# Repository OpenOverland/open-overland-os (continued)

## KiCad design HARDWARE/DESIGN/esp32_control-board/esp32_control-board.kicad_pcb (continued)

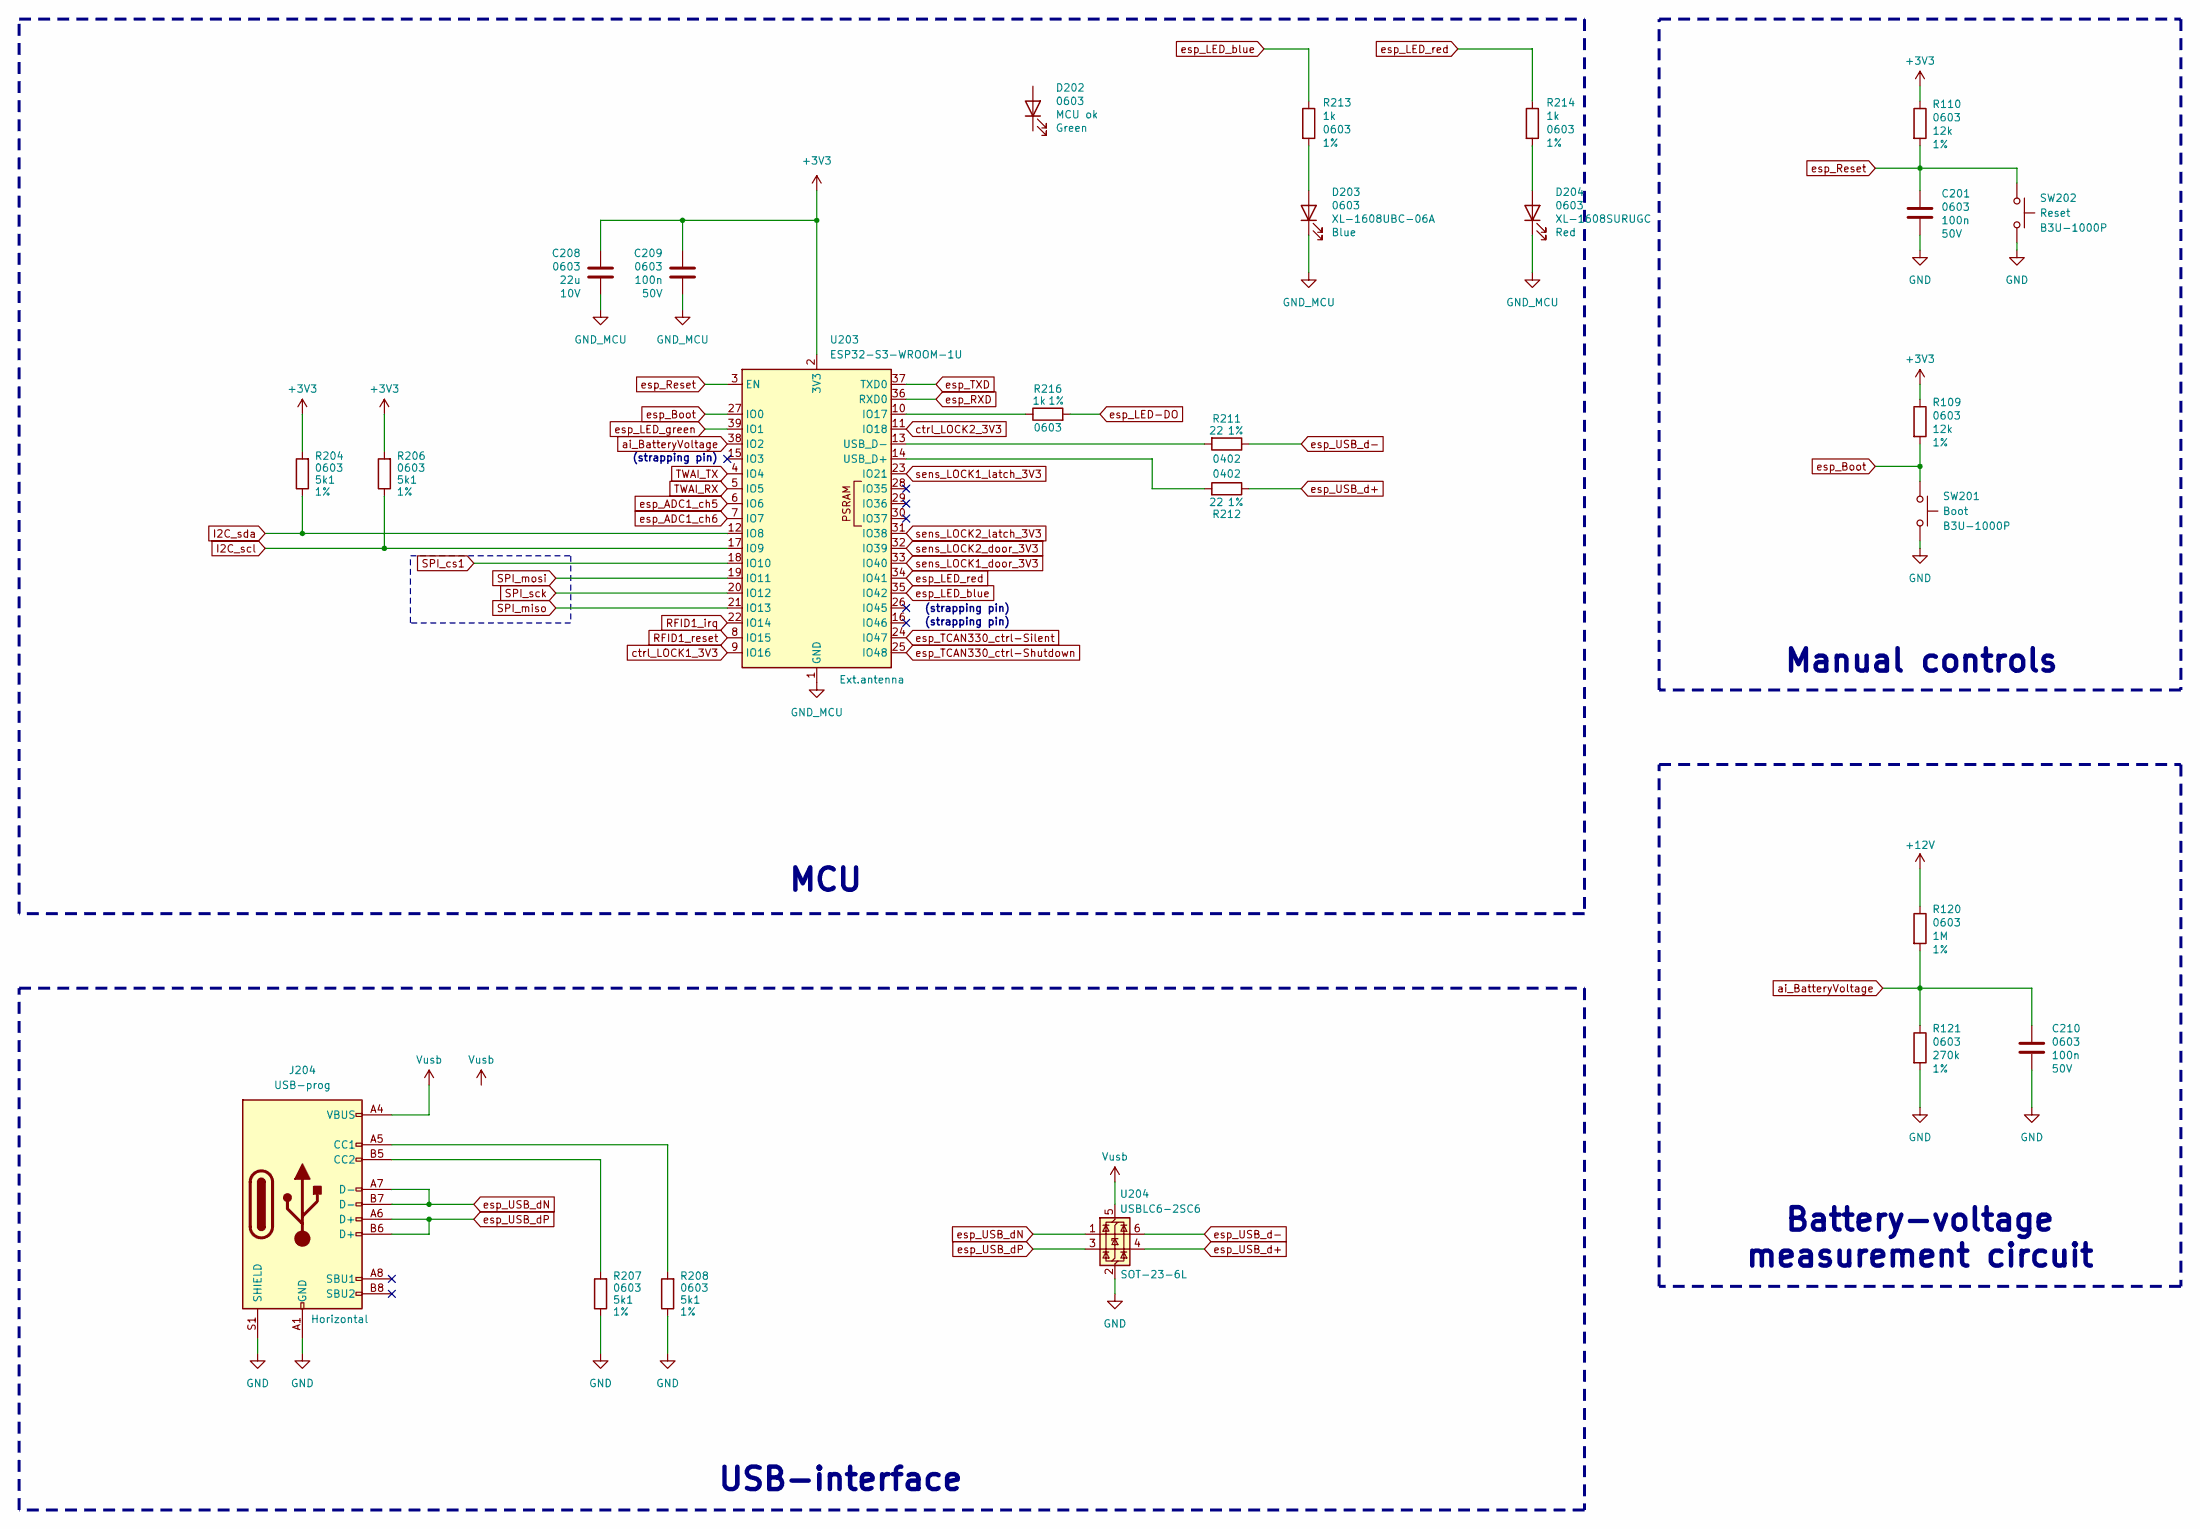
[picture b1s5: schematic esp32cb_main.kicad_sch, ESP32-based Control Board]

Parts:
C201, C209, C210: 100n; C_0603_1608Metric; LCSC part C1591
C208: 22u; C_0805_2012Metric; LCSC C907991
D202: MCU ok; LED_0603_1608Metric; LCSC part C965804
D203: XL-1608UBC-06A; LED_0603_1608Metric; LCSC C7371904
D204: XL-1608SURUGC; LED_0603_1608Metric; LCSC C5349934
J204: USB-prog; C3151749_USB_TYPE-C_Vertical
R109, R110: 12k; R_0603_1608Metric; LCSC C114659
R120: 1M; R_0603_1608Metric; LCSC C22935
R121: 270k; R_0603_1608Metric; LCSC C22965
R204, R206, R207, R208: 5k1; R_0603_1608Metric; LCSC part C2907044
R211, R212: 22; R_0402_1005Metric; LCSC part C114765
R213, R214, R216: 1k; R_0603_1608Metric; LCSC part C21190
SW201: Boot; SW_SPST_B3U-1000P; LCSC part C231329
SW202: Reset; SW_SPST_B3U-1000P; LCSC part C231329
U203: ESP32-S3-WROOM-1U; LCSC C3013946
U204: USBLC6-2SC6; SOT-23-6; LCSC part C7519

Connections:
+3V3: C208.2, C209.2, R109.1, R110.1, R204.2, R206.2, U203.2 (3V3); also elsewhere on the board
+12V: R120.1; also elsewhere on the board
GND: C201.1, C210.1, J204.A1 (GND), J204.A12 (GND), J204.B1 (GND), J204.B12 (GND), J204.S1 (SHIELD), R121.2, R207.1, R208.1, SW201.2, SW202.2, U204.2 (GND); also elsewhere on the board
GND_MCU: C208.1, C209.1, D203.1 (K), D204.1 (K), U203.1 (GND), U203.40 (GND), U203.41 (GND); also elsewhere on the board
I2C_scl: R206.1, U203.17 (IO9); also elsewhere on the board
I2C_sda: R204.1, U203.12 (IO8); also elsewhere on the board
unnamed: D203.2 (A), R213.2
unnamed: D204.2 (A), R214.2
unnamed: J204.A5 (CC1), R208.2
unnamed: J204.B5 (CC2), R207.2
unnamed: R216.1, U203.10 (IO17)
unnamed: R212.2, U203.14 (USB_D+)
unnamed: R211.2, U203.13 (USB_D-)
RFID1_irq: U203.22 (IO14); also elsewhere on the board
RFID1_reset: U203.8 (IO15); also elsewhere on the board
SPI_cs1: U203.18 (IO10); also elsewhere on the board
SPI_miso: U203.21 (IO13); also elsewhere on the board
SPI_mosi: U203.19 (IO11); also elsewhere on the board
SPI_sck: U203.20 (IO12); also elsewhere on the board
TWAI_RX: U203.5 (IO5); also elsewhere on the board
TWAI_TX: U203.4 (IO4); also elsewhere on the board
Vusb: J204.A4 (VBUS), J204.A9 (VBUS), J204.B4 (VBUS), J204.B9 (VBUS), U204.5 (VBUS); also elsewhere on the board
ai_BatteryVoltage: C210.2, R120.2, R121.1, U203.38 (IO2)
ctrl_LOCK1_3V3: U203.9 (IO16); also elsewhere on the board
ctrl_LOCK2_3V3: U203.11 (IO18); also elsewhere on the board
esp_ADC1_ch5: U203.6 (IO6); also elsewhere on the board
esp_ADC1_ch6: U203.7 (IO7); also elsewhere on the board
esp_Boot: R109.2, SW201.1, U203.27 (IO0)
esp_LED-DO: R216.2; also elsewhere on the board
esp_LED_blue: R213.1, U203.35 (IO42)
esp_LED_green: U203.39 (IO1)
esp_LED_red: R214.1, U203.34 (IO41)
esp_RXD: U203.36 (RXD0); also elsewhere on the board
esp_Reset: C201.2, R110.2, SW202.1, U203.3 (EN)
esp_TCAN330_ctrl-Shutdown: U203.25 (IO48); also elsewhere on the board
esp_TCAN330_ctrl-Silent: U203.24 (IO47); also elsewhere on the board
esp_TXD: U203.37 (TXD0); also elsewhere on the board
esp_USB_d+: R212.1, U204.4 (I/O2)
esp_USB_d-: R211.1, U204.6 (I/O1)
esp_USB_dN: J204.A7 (D-), J204.B7 (D-), U204.1 (I/O1)
esp_USB_dP: J204.A6 (D+), J204.B6 (D+), U204.3 (I/O2)
sens_LOCK1_door_3V3: U203.33 (IO40); also elsewhere on the board
sens_LOCK1_latch_3V3: U203.23 (IO21); also elsewhere on the board
sens_LOCK2_door_3V3: U203.32 (IO39); also elsewhere on the board
sens_LOCK2_latch_3V3: U203.31 (IO38); also elsewhere on the board

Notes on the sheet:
Battery-voltage measurement circuit
(strapping pin)
USB-interface
MCU
Manual controls

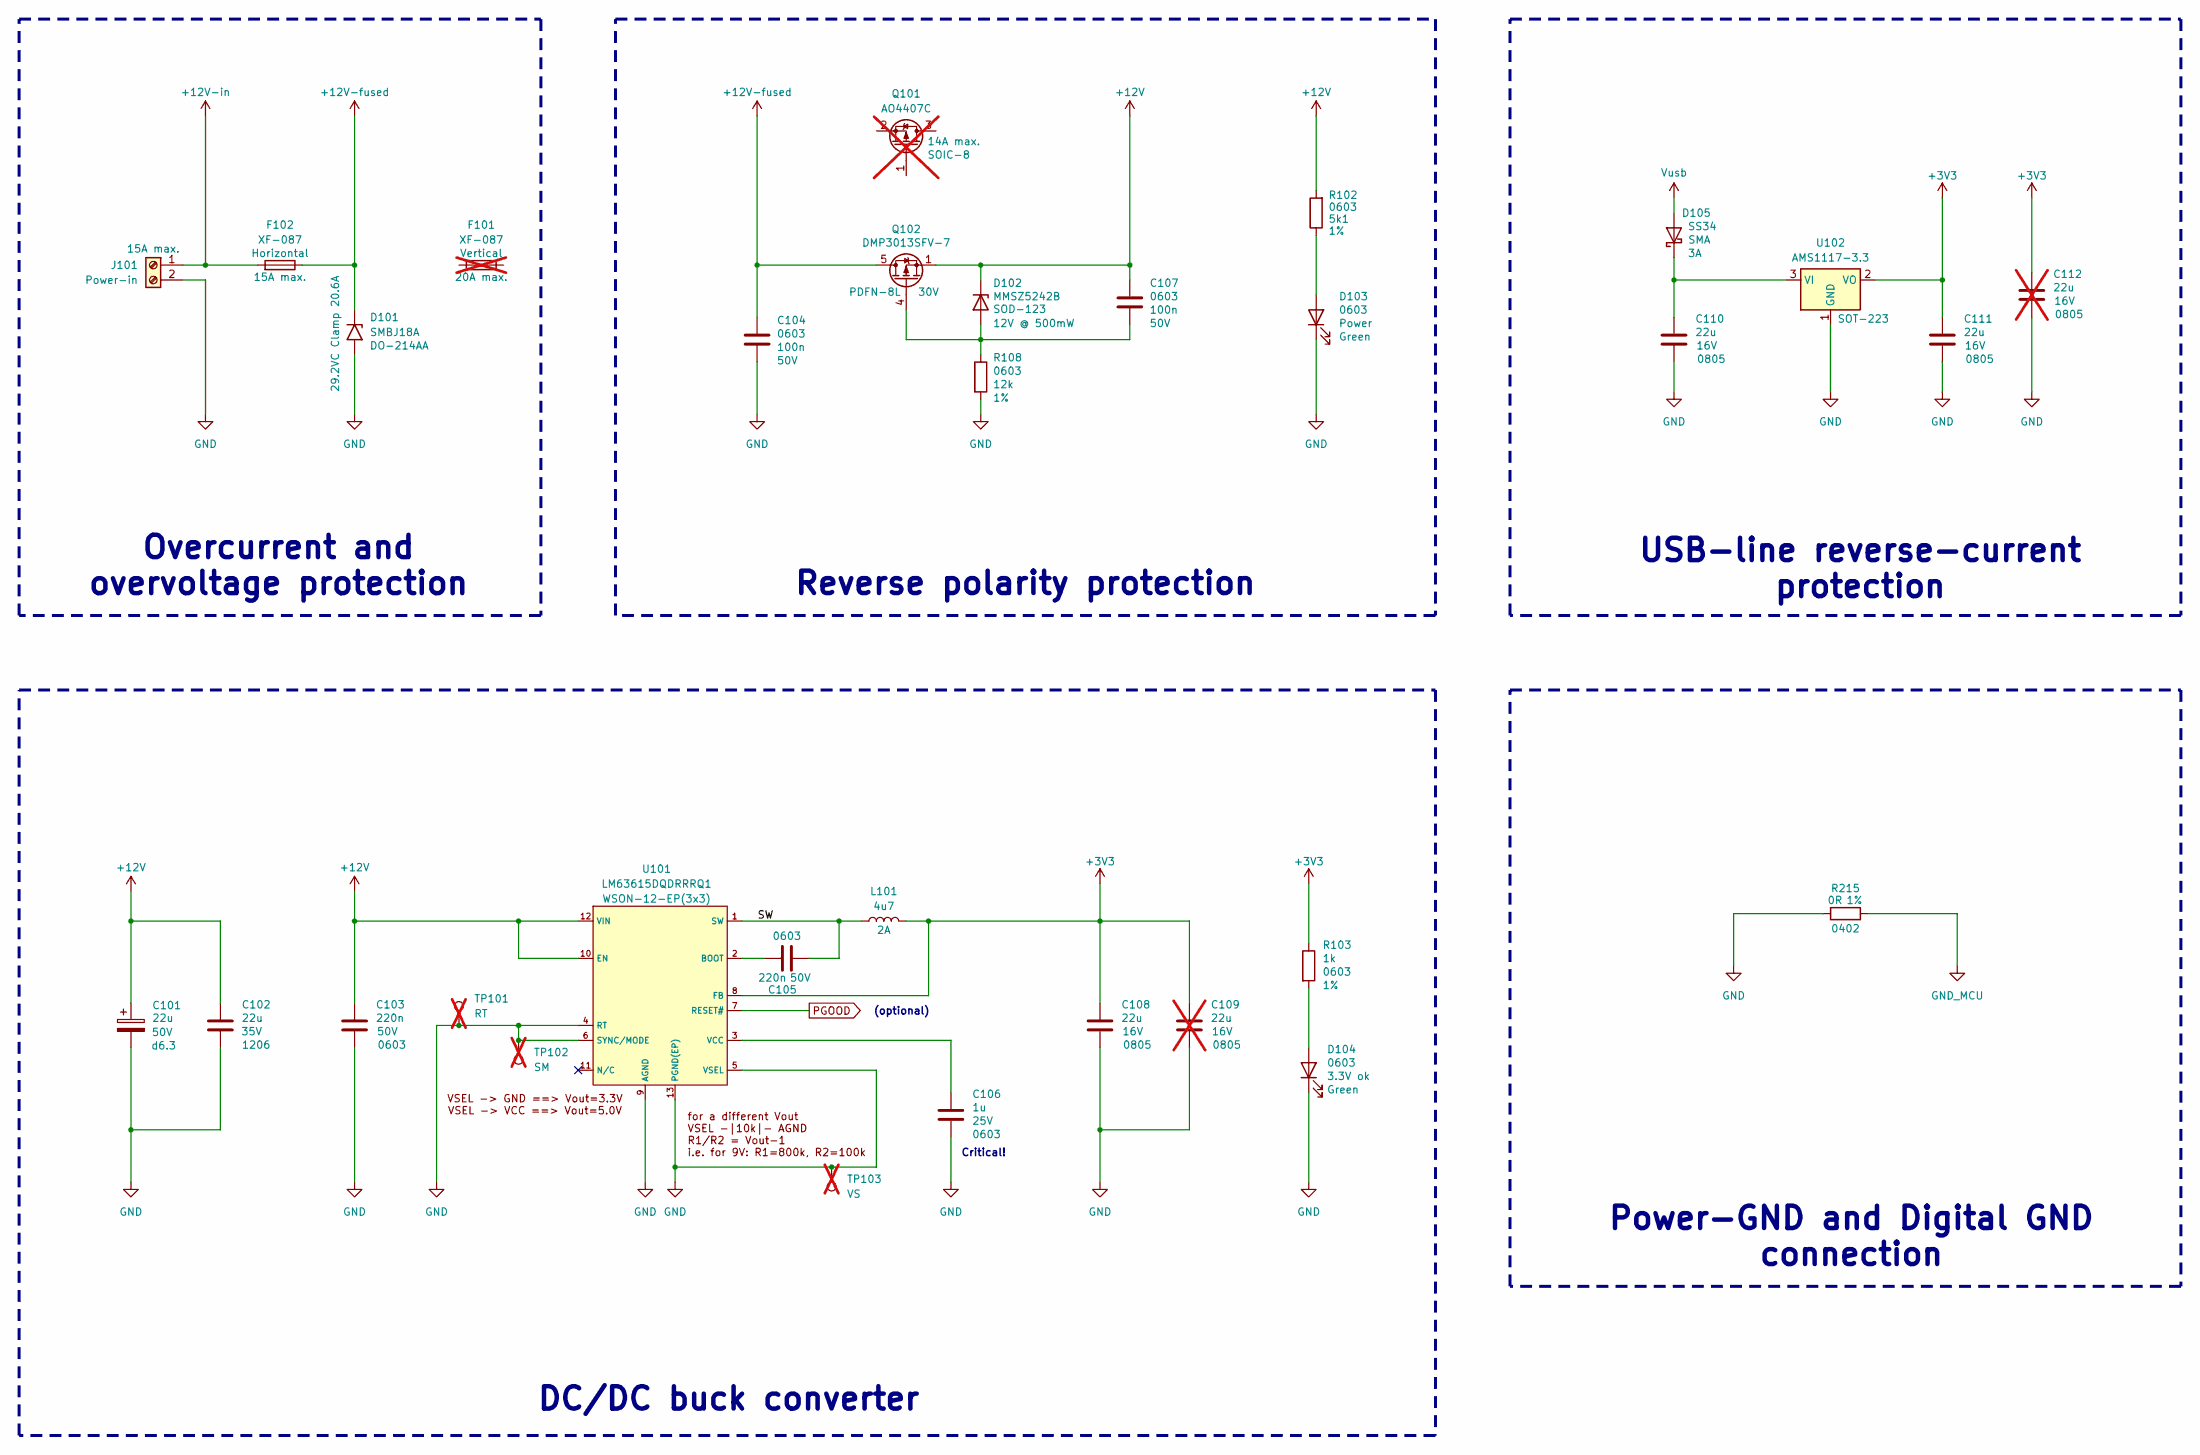
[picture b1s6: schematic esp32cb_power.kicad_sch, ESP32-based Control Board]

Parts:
C101: 22u; CP_Elec_6.3x5.7; LCSC part C2983377
C102: 22u; C_1206_3216Metric; LCSC part C342620
C103, C105: 220n; C_0603_1608Metric; LCSC part C64705
C104, C107: 100n; C_0603_1608Metric; LCSC part C1591
C106: 1u; C_0603_1608Metric; LCSC part C29936
C108, C110, C111: 22u; C_0805_2012Metric; LCSC part C98190
C109, C112: 22u; C_0805_2012Metric; LCSC part C98190; not fitted
D101: SMBJ18A; D_SMB; LCSC C151256
D102: MMSZ5242B; D_SOD-123; LCSC C82050
D103: Power; LED_0603_1608Metric; LCSC part C965804
D104: 3.3V ok; LED_0603_1608Metric; LCSC part C965804
D105: SS34; D_SMA; LCSC part C908680
F101: XF-087; FuseHolder_Blade_ATO_Littelfuse_FLR_178.6165; LCSC C41371864; not fitted
F102: XF-087; C206906_LittleFuse_01530007Z; LCSC C206906
J101: Power-in; AMASS_XT30PW-M_1x02_P2.50mm_Horizontal; LCSC C431092
L101: 4u7; L_Taiyo-Yuden_MD-4040; LCSC part C167828
Q101: AO4407C; SOIC-8_P-MOSFET; LCSC C469397; not fitted
Q102: DMP3013SFV-7; Diodes_PowerDI3333-8; LCSC C264098
R102: 5k1; R_0603_1608Metric; LCSC part C2907044
R103: 1k; R_0603_1608Metric; LCSC part C21190
R108: 12k; R_0603_1608Metric; LCSC C114659
R215: 0R; R_0402_1005Metric; LCSC C106231
TP101: RT; TestPoint_THTPad_D1.0mm_Drill0.5mm; not fitted
TP102: SM; TestPoint_THTPad_D1.0mm_Drill0.5mm; not fitted
TP103: VS; TestPoint_THTPad_D1.0mm_Drill0.5mm; not fitted
U101: LM63615DQDRRRQ1; WSON-12-1EP_3x3mm_P0.5mm_EP1.5x2.5mm; LCSC part C2873346
U102: AMS1117-3.3; SOT-223-3_TabPin2; LCSC C6186

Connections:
+3V3: C108.1, C109.1, C111.1, C112.1, L101.1, R103.1, U101.8 (FB), U102.2 (VO); also elsewhere on the board
+12V: C101.1, C102.1, C103.1, C107.2, D102.1 (K), Q102.1 (S), Q102.2 (S), Q102.3 (S), R102.2, U101.10 (EN), U101.12 (VIN); also elsewhere on the board
+12V-fused: C104.2, D101.1 (A1), F102.1, Q102.5 (D)
+12V-in: F102.2, J101.1
/Power/SW: C105.2, L101.2, U101.1 (SW)
GND: C101.2, C102.2, C103.2, C104.1, C106.2, C108.2, C109.2, C110.2, C111.2, C112.2, D101.2 (A2), D103.1 (K), D104.1 (K), J101.2, R108.2, R215.2, TP101.1 (1_1), TP102.1 (1_1), TP103.1 (1_1), U101.4 (RT), U101.5 (VSEL), U101.6 (SYNC/MODE), U101.9 (AGND), U101.13 (PGND(EP)), U102.1 (GND); also elsewhere on the board
GND_MCU: R215.1; also elsewhere on the board
unnamed: C107.1, D102.2 (A), Q102.4 (G), R108.1
unnamed: D103.2 (A), R102.1
unnamed: D104.2 (A), R103.2
unnamed: C110.1, D105.1 (K), U102.3 (VI)
unnamed: C105.1, U101.2 (BOOT)
unnamed: C106.1, U101.3 (VCC)
PGOOD: U101.7 (RESET#)
Vusb: D105.2 (A); also elsewhere on the board

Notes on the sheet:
Power-GND and Digital GND connection
(optional)
DC/DC buck converter
Critical!
Overcurrent and overvoltage protection
USB-line reverse-current protection
Reverse polarity protection

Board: 2 copper layers, 143 parts (0 on the bottom side), 98 nets, no tracks yet.
